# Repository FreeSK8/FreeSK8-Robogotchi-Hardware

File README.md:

# FreeSK8-Robogotchi-Hardware

The [FreeSK8 Robogotchi](https://derelictrobot.com/collections/production/products/freesk8-robogotchi) is an advanced BLE Receiver, Datalogger, and core component of the FreeSK8 System.

Think of it like a blackbox flight recorder for your esk8 or LEV. 

The Robogotchi brings Always-On Logging as a core feature with an asynchronous logging integration with our FreeSK8 Mobile App. 

Ride now, Sync later.

[Robogotchi Documentation @ FreeSK8 Codex](https://codex.freesk8.org/docs/robogotchi)
 
<!-- LICENSE -->
## License

(C) Copyright 2021 - FreeSK8 Foundation NPO

**Licensed under [CERN-OHL-S V2.0](https://ohwr.org/cern_ohl_s_v2.txt)**

https://cern-ohl.web.cern.ch/

<!-- CONTACT -->
## Authors

* Renee Glinski - [@r3n33](https://github.com/r3n33)
* Andrew Dresner - [@DerelictRobot](https://github.com/DerelictRobot)
* Project Link: [https://github.com/FreeSK8](https://github.com/FreeSK8)

 <!-- CONTRIBUTING -->
## Contributing

Contributions are what make the open source community such an amazing place to be learn, inspire, and create. Any contributions you make are **greatly appreciated**.

1. Fork the Project
2. Create your Feature Branch (`git checkout -b feature/AmazingFeature`)
3. Commit your Changes (`git commit -m 'Add some AmazingFeature'`)
4. Push to the Branch (`git push origin feature/AmazingFeature`)
5. Open a Pull Request

<!-- ACKNOWLEDGEMENTS -->
## Attribution & References

* [VESC-Project](https://vesc-project.com)
* [NRF52 VESC](https://github.com/vedderb/nrf52_vesc)
* [Nordic NRF5 SDK](https://infocenter.nordicsemi.com/index.jsp)

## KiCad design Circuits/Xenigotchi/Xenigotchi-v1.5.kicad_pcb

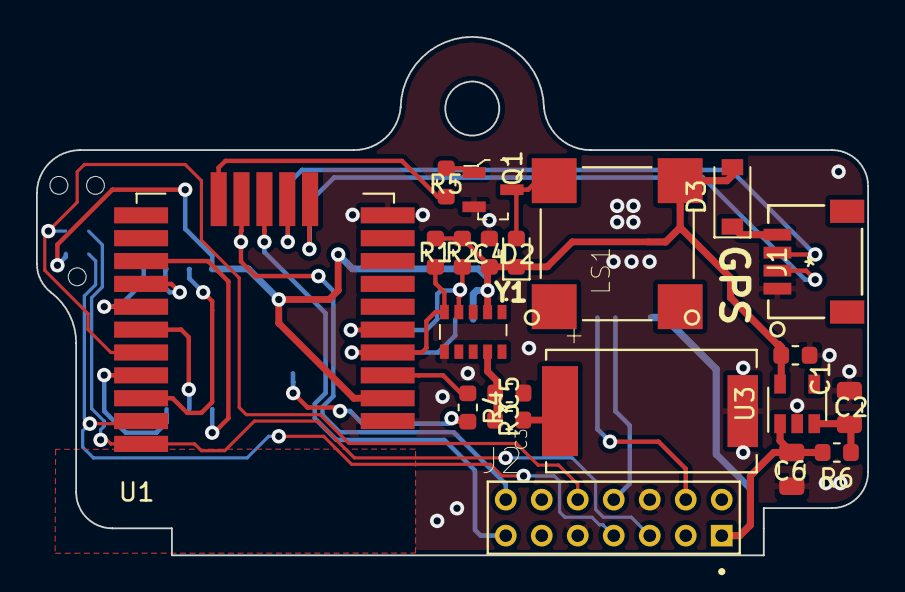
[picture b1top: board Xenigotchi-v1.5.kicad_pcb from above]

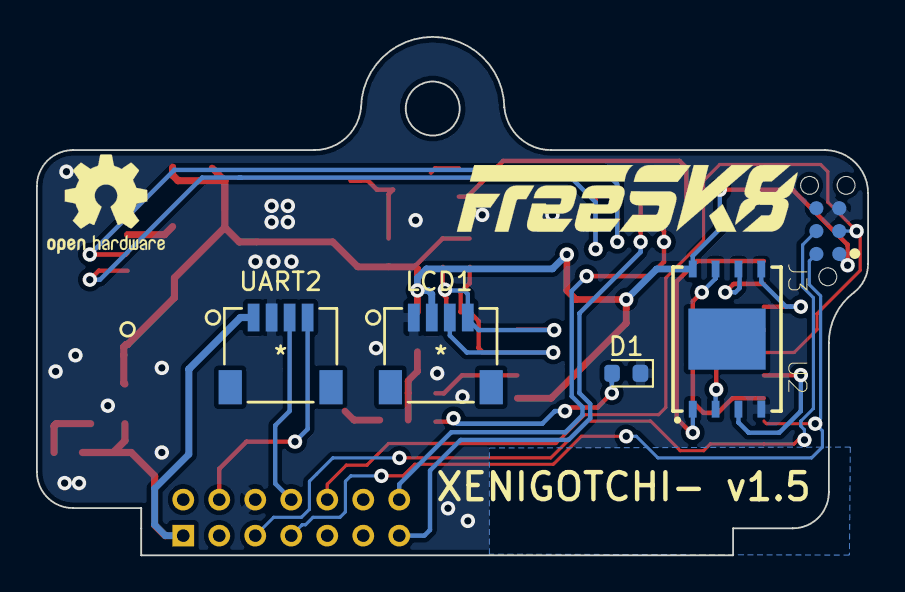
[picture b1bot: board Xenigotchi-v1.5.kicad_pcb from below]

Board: 2 copper layers, 46.2 x 28.8 mm, 26 parts (5 on the bottom side), 29 nets.

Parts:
C1: 1.0uF; C_0603_1608Metric
C2, C6: 10uF; C_0805_2012Metric
C3: DSK-3R3H224U-HL; CAP_DSK-3R3H224U-HL
C4: 0.1uF; C_0603_1608Metric
C5: 10000pF; C_0603_1608Metric
D1: LED; LED_0603_1608Metric
D2: SD0603S040S0R2; D_0603_1608Metric
D3: D_Schottky_Small; D_SOD-123
J1: SM04B-SRSS-TB
J2: 1-1734508-4; TE_1-1734508-4
J3: TC2030-CTX; TAG_TC2030-IDC-NL
LCD1: SM04B-SRSS-TB
LS1: CMT-8503-90-SMT-TR; XDCR_CMT-8503-90-SMT-TR
Q1: 2SD1484KT146R; SOT-23-3
R1, R2: 10k; R_0603_1608Metric
R3: 470r; R_0603_1608Metric
R4: 1k; R_0603_1608Metric
R5: 180r; R_0603_1608Metric
R6: 20k; R_0603_1608Metric
U1: SKB501; SKB501_RF_Module
U2: W25N01GVZEIG_TR; SON127P800X600X80-9N
U3: TLV75533PDBV; SOT-23-5
UART2: SM04B-SRSS-TB
Y1: RV-3129-C3; ABRTCMC32768kHzEOZ9S3DBT

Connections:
+3V3: C1.1, C4.1, D2.1, D3.2, J3.1, LCD1.2, LS1.P, R1.1, R2.1, U1.2, U2.8, U3.5, Y1.2
+5V: C6.1, J2.1, R6.2, U3.1, UART2.1
/ESC-RX: J2.7, U1.13
/ESC-TX: J2.14, U1.14
/GPS-RX: J1.3, U1.12
/GPS-TX: J1.2, U1.11
/P0.05: R4.1, U1.3
/P0.08: R5.2, U1.15
/P0.17: U1.18, U2.1
/P0.19: U1.19, U2.6
/P0.20: U1.20, U2.5
/P0.21: U1.21, U2.2
/P0.22: U1.23, U2.3
/P0.23: U1.24, U2.7
/RST: J2.12, J3.3, U1.22
/SCL: LCD1.4, R2.2, U1.5, Y1.4
/SDA: LCD1.3, R1.2, U1.4, Y1.5
/SWCLK: J2.3, J3.4, U1.26
/SWDIO: J2.4, J3.2, U1.25
/UART2-RX: J2.11, UART2.3
/UART2-TX: J2.9, UART2.4
/VBACKUP: C5.1, R3.1, Y1.9
GND: C1.2, C2.2, C3.2, C4.2, C5.2, C6.2, D1.1, J1.1, J2.5, J2.10, J3.5, LCD1.1, Q1.1, U1.1, U1.10, U2.4, U3.2, UART2.2, Y1.6
unnamed: C2.1, R6.1, U3.3
unnamed: C3.1, R3.2
unnamed: D1.2, R4.2
unnamed: D2.2, LS1.N, Q1.3
unnamed: D3.1, J1.4
unnamed: Q1.2, R5.1

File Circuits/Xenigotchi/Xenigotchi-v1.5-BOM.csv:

Comment,Designator,Footprint,LCSC Part #
"1.0uF Unpolarized capacitor, small symbol",C1,C_0603_1608Metric,
"10uF Unpolarized capacitor, small symbol","C2,C6",C_0805_2012Metric,
DSK-3R3H224U-HL ,C3,CAP_DSK-3R3H224U-HL,
"0.1uF Unpolarized capacitor, small symbol",C4,C_0603_1608Metric,
"10000pF Unpolarized capacitor, small symbol",C5,C_0603_1608Metric,
LED Light emitting diode,D1,LED_0603_1608Metric,
SD0603S040S0R2 Schottky diode,D2,D_0603_1608Metric,
"D_Schottky_Small Schottky diode, small symbol",D3,D_SOD-123,
SM04B-SRSS-TB ,"J1,LCD1,UART2",SM04B-SRSS-TB,
1-1734508-4 ,J2,TE_1-1734508-4,
TC2030-CTX ,J3,TAG_TC2030-IDC-NL,
CMT-8503-90-SMT-TR ,LS1,XDCR_CMT-8503-90-SMT-TR,
2SD1484KT146R ,Q1,SOT-23-3,
"10k Resistor, small US symbol","R1,R2",R_0603_1608Metric,
"470r Resistor, small US symbol",R3,R_0603_1608Metric,
"1k Resistor, small US symbol",R4,R_0603_1608Metric,
"180r Resistor, small US symbol",R5,R_0603_1608Metric,
"20k Resistor, small US symbol",R6,R_0603_1608Metric,
SKB501 ,U1,SKB501_RF_Module,
W25N01GVZEIG_TR ,U2,SON127P800X600X80-9N,
"TLV75533PDBV 500mA Low Dropout Voltage Regulator, Fixed Output 3.3V, SOT-23-5",U3,SOT-23-5,
RV-3129-C3 ,Y1,ABRTCMC32768kHzEOZ9S3DBT,

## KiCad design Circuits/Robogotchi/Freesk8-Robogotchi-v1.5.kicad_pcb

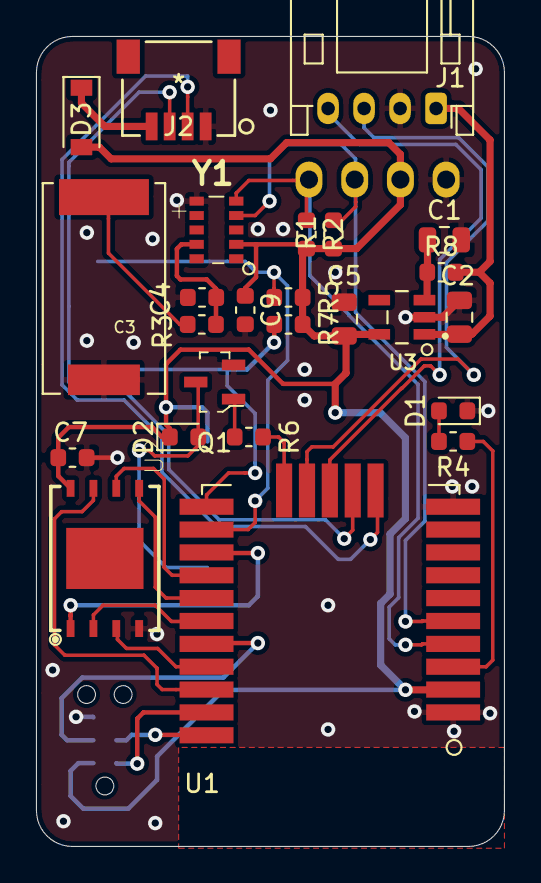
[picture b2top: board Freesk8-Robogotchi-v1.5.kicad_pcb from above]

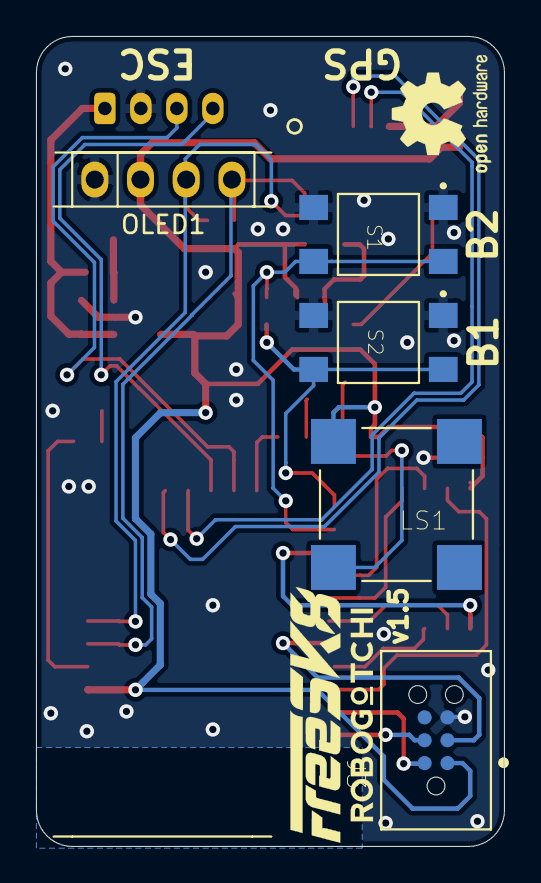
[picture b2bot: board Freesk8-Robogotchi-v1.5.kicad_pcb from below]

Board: 2 copper layers, 26.0 x 45.0 mm, 30 parts (5 on the bottom side), 29 nets.

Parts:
C1: 10uF; C_0805_2012Metric
C2, C5: 1uF; C_0805_2012Metric
C3: DSK-3R3H224U-HL; CAP_DSK-3R3H224U-HL
C4: 10000pF; C_0603_1608Metric
C7, C9: 0.1uF; C_0603_1608Metric
D1: LED; LED_0603_1608Metric
D2: SD0603S040S0R2; D_0603_1608Metric
D3: B130-E3; D_SOD-123
J1: S4B-PH-K-SLFSN; JST_PH_S4B-PH-K_1x04_P2.00mm_Horizontal
J2: SM04B-SRSS-TB
J3: TC2030-CTX; TAG_TC2030-IDC-NL
LS1: CMT-8503-90-SMT-TR; XDCR_CMT-8503-90-SMT-TR
OLED1: OLED-0.91; OLED-0.9
Q1: 2SD1484KT146R; SOT-23-3-R
R1, R2, R5, R7: 10k; R_0603_1608Metric
R3: 470r; R_0603_1608Metric
R4: 1k; R_0603_1608Metric
R6: 180r; R_0603_1608Metric
R8: 20k; R_0603_1608Metric
S1, S2: TL3315NF160Q; SW_TL3305AF260QG
U1: SKB501; SKB501_RF_Module
U2: MX25L25645GZ2I-08G; SON127P800X600X80-9N
U3: TLV75533PDBVR; SOT95P280X145-5N
Y1: RV-3129-C3; ABRTCMC32768kHzEOZ9S3DBT

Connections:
+3V3: C5.1, C7.1, C9.1, D2.1, D3.2, J3.1, LS1.P, OLED1.2, R1.1, R2.1, R5.1, R7.1, U1.2, U2.8, U3.5, Y1.2
+5V: C2.1, J1.1, R8.2, U3.1
/ESC-RX: J1.3, U1.14
/ESC-TX: J1.4, U1.13
/GPS-RX: J2.3, U1.12
/GPS-TX: J2.2, U1.11
/P0.05: R4.1, U1.3
/P0.08: R6.2, U1.15
/P0.09: R7.2, S2.3, S2.4, U1.16
/P0.10: R5.2, S1.3, S1.4, U1.17
/P0.17: U1.18, U2.1
/P0.19: U1.19, U2.6
/P0.20: U1.20, U2.5
/P0.21: U1.21, U2.2
/P0.22: U1.23, U2.3
/P0.23: U1.24, U2.7
/RST: J3.3, U1.22
/SCL: OLED1.3, R2.2, U1.5, Y1.4
/SDA: OLED1.4, R1.2, U1.4, Y1.5
/SWCLK: J3.4, U1.26
/SWDIO: J3.2, U1.25
/VBACKUP: C4.1, R3.1, Y1.9
GND: C1.2, C2.2, C3.2, C4.2, C5.2, C7.2, C9.2, D1.1, J1.2, J2.1, J3.5, OLED1.1, Q1.1, S1.1, S1.2, S2.1, S2.2, U1.1, U1.10, U2.4, U3.2, Y1.6
unnamed: C1.1, R8.1, U3.3
unnamed: C3.1, R3.2
unnamed: D1.2, R4.2
unnamed: D2.2, LS1.N, Q1.3
unnamed: D3.1, J2.4
unnamed: Q1.2, R6.1

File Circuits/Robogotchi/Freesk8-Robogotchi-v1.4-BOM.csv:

"Id";"Designator";"Package";"Quantity";"Designation";"Supplier and ref";
1;"Q1";"SOT-23-3-R";1;"2SD1484KT146R";;;
2;"G***";"FreeSK8-Logo-14x3.5mm";1;"LOGO";;;
3;"OLED1";"OLED-0.9";1;"OLED-0.91";;;
4;"C7,C9";"C_0603_1608Metric";2;"0.1uF";;;
5;"J3";"TAG_TC2030-IDC-NL";1;"TC2030-CTX";;;
6;"S2,S1";"SW_TL3305AF260QG";2;"TL3315NF160Q";;;
7;"C3";"CAP_DSK-3R3H224U-HL";1;"DSK-3R3H224U-HL";;;
8;"Y1";"ABRTCMC32768kHzEOZ9S3DBT";1;"RV-3129-C3";;;
9;"J2,J1";"JST_PH_S4B-PH-K_1x04_P2.00mm_Horizontal";2;"S4B-PH-K-SLFSN";;;
10;"C5,C2";"C_0805_2012Metric";2;"10uF";;;
11;"C4";"C_0603_1608Metric";1;"10000pF";;;
12;"LS1";"XDCR_CMT-8503-90-SMT-TR";1;"CMT-8503-90-SMT-TR";;;
13;"R6";"R_0603_1608Metric";1;"180r";;;
14;"D2,D3";"D_0603_1608Metric";2;"SD0603S040S0R2";;;
15;"D1";"LED_0603_1608Metric";1;"LED";;;
16;"R4";"R_0603_1608Metric";1;"1k";;;
17;"U2";"SON127P800X600X80-9N";1;"MX25L25645GZ2I-08G";;;
18;"R7,R1,R2,R5";"R_0603_1608Metric";4;"10k";;;
19;"C1,C6";"C_0603_1608Metric";2;"1.0uF";;;
20;"R3";"R_0603_1608Metric";1;"470r";;;
21;"IC1";"SON65P200X200X80-7N";1;"LP5912-3.3DRVR";;;
22;"U1";"SKB501_RF_Module";1;"SKB501";;;

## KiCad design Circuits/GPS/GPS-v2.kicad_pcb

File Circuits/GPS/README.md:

## GPS v1.3 utilizes an off the shelf GPS solution, such as the BN-220 GPS Module.

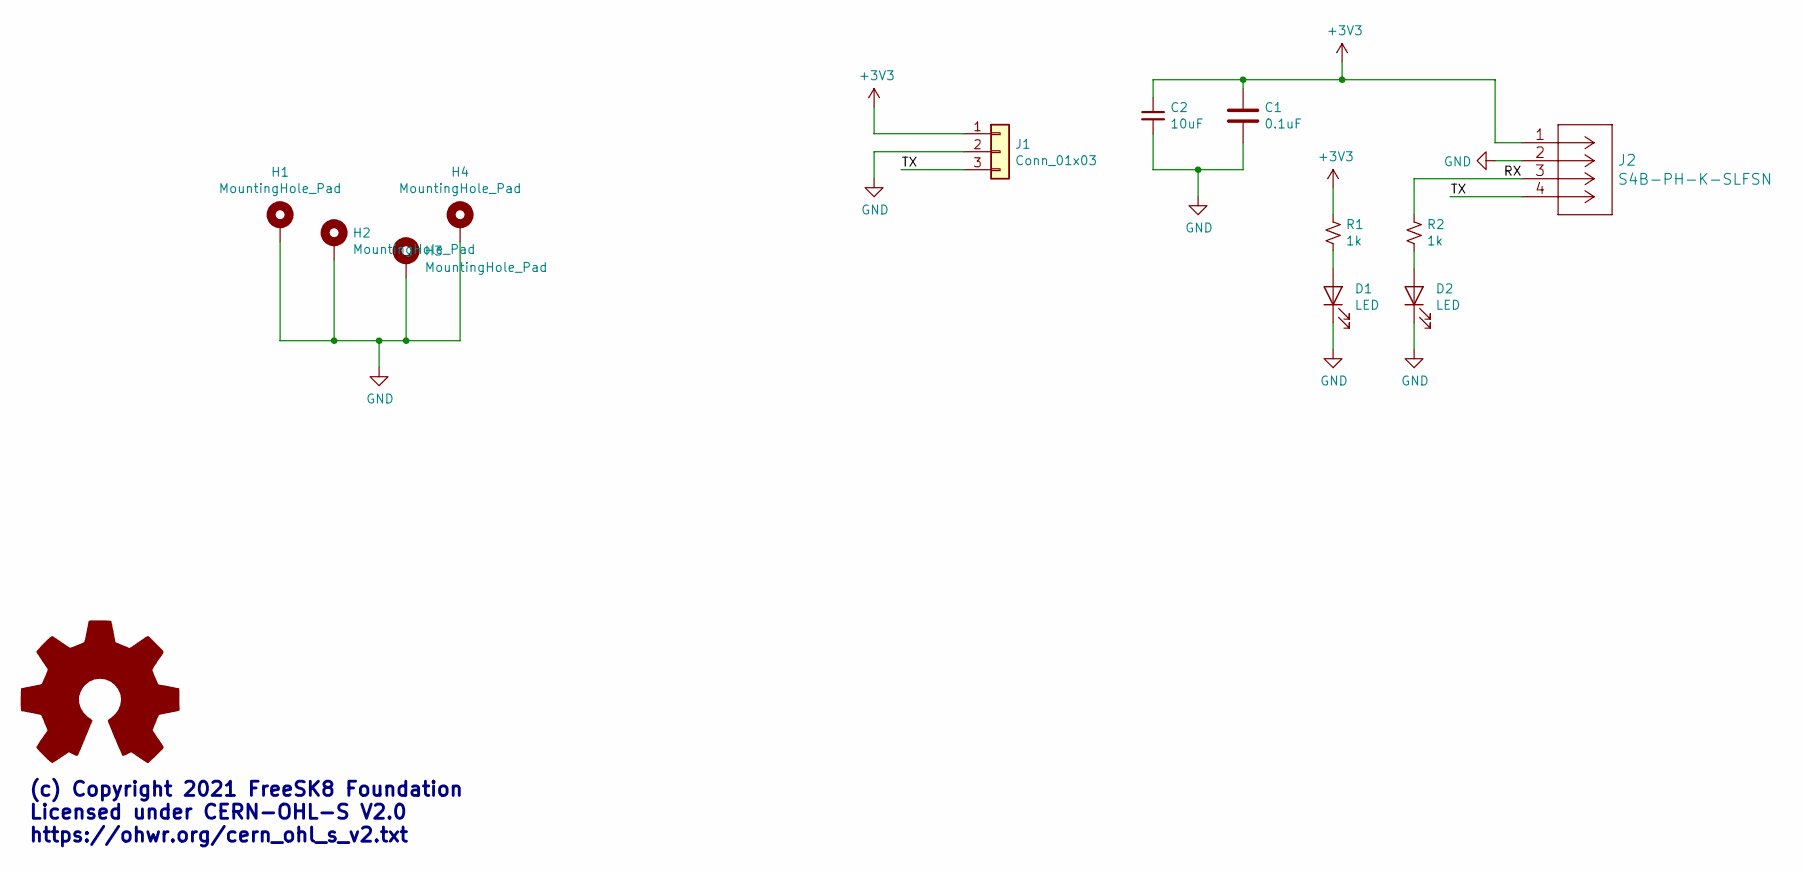
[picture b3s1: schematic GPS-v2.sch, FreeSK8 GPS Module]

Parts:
C1: 0.1uF; C_0603_1608Metric
C2: 10uF; C_0805_2012Metric
D1, D2: LED; LED_0603_1608Metric
H1, H2, H3, H4: MountingHole_Pad; MountingHole_2.5mm_Pad
J1: Conn_01x03; JST_SH_SM03B-SRSS-TB_1x03-1MP_P1.00mm_Horizontal
J2: S4B-PH-K-SLFSN; JST_PH_S4B-PH-K_1x04_P2.00mm_Horizontal
R1, R2: 1k; R_0603_1608Metric

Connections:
+3V3: C1.1, C2.1, J1.1, J2.1, R1.1
/RX: J2.3, R2.1
/TX: J1.3, J2.4
GND: C1.2, C2.2, D1.1 (K), D2.1 (K), H1.1, H2.1, H3.1, H4.1, J1.2, J2.2
unnamed: D1.2 (A), R1.2
unnamed: D2.2 (A), R2.2

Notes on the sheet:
(c) Copyright 2021 FreeSK8 Foundation Licensed under CERN-OHL-S V2.0 https://ohwr.org/cern_ohl_s_v2.txt

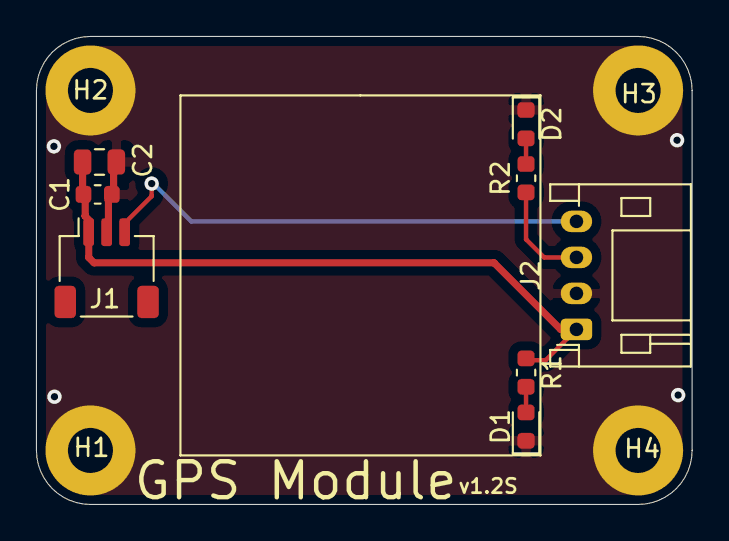
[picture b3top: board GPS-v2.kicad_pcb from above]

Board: 2 copper layers, 36.4 x 26.0 mm, 12 parts (0 on the bottom side), 6 nets.

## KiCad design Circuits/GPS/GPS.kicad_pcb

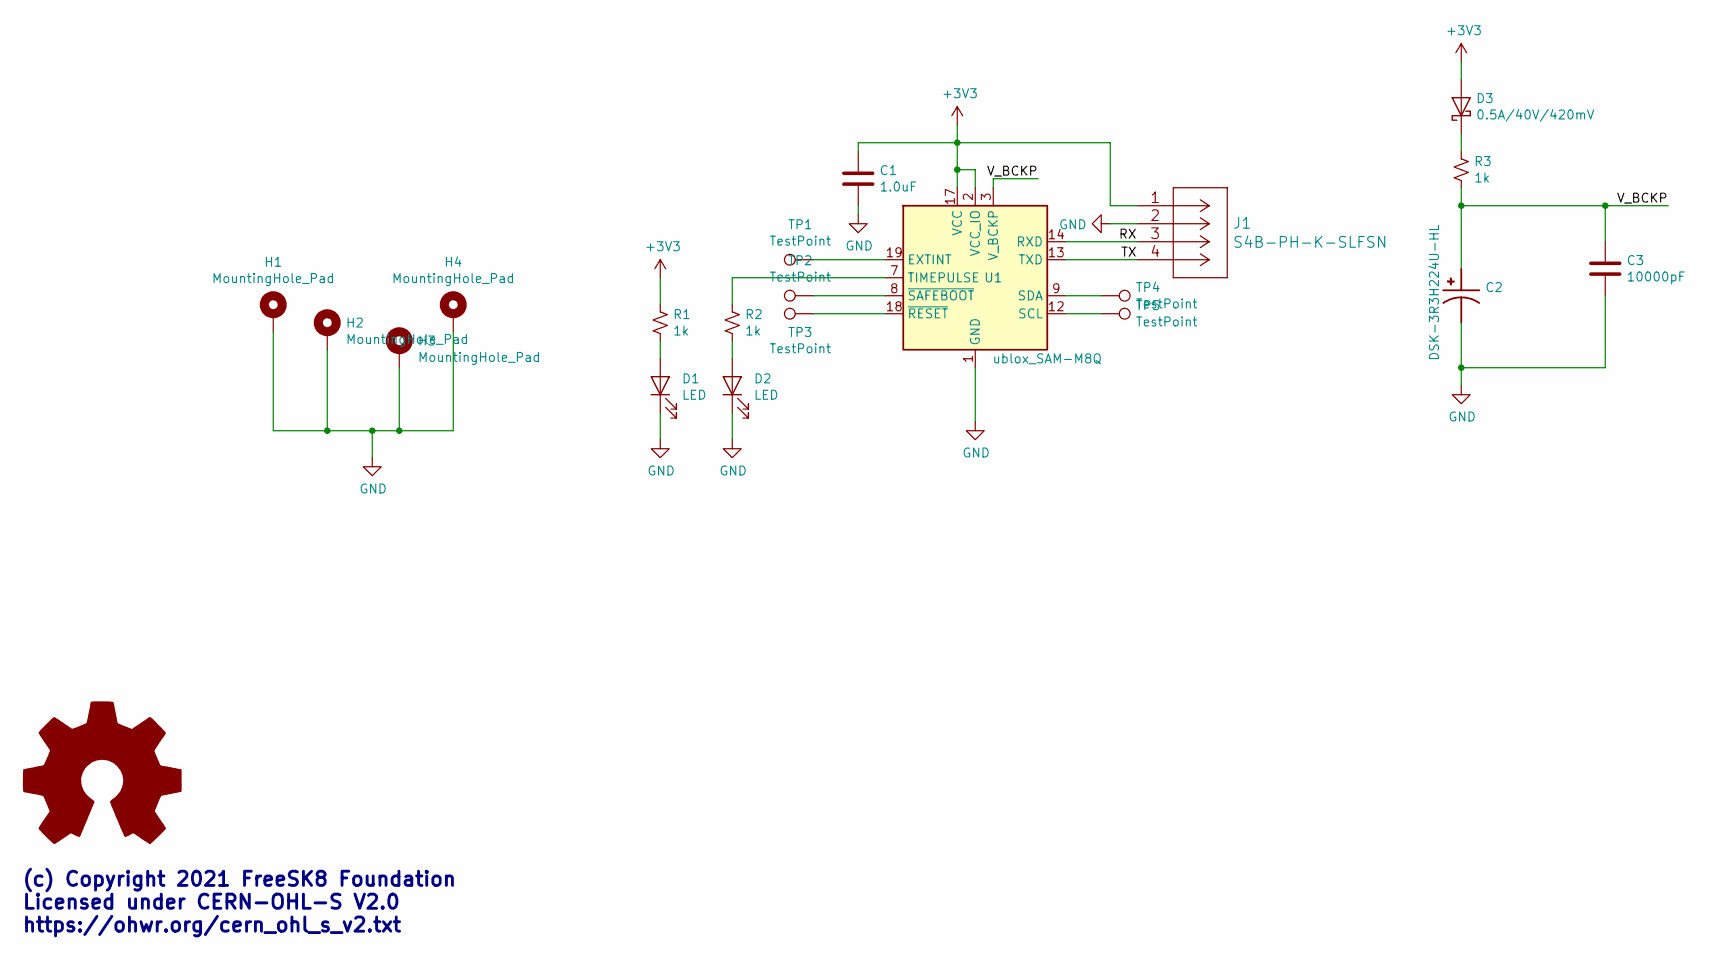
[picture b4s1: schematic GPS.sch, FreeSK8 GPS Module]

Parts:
C1: 1.0uF; C_0603_1608Metric
C2: DSK-3R3H224U-HL; CAP_DSK-3R3H224U-HL
C3: 10000pF; C_0603_1608Metric
D1, D2: LED; LED_0603_1608Metric
D3: 0.5A/40V/420mV; D_0603_1608Metric
H1, H2, H3, H4: MountingHole_Pad; MountingHole_2.5mm_Pad
J1: S4B-PH-K-SLFSN; JST_PH_S4B-PH-K_1x04_P2.00mm_Horizontal
R1, R2, R3: 1k; R_0603_1608Metric
TP1, TP2, TP3, TP4, TP5: TestPoint; TestPoint_Pad_1.0x1.0mm
U1: ublox_SAM-M8Q; ublox_SAM-M8Q_HandSolder

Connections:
+3V3: C1.1, D3.2 (A), J1.1, R1.1, U1.2 (VCC_IO), U1.17 (VCC)
/RX: J1.3, U1.14 (RXD)
/TX: J1.4, U1.13 (TXD)
/V_BCKP: C2.1, C3.1, R3.2, U1.3 (V_BCKP)
GND: C1.2, C2.2, C3.2, D1.1 (K), D2.1 (K), H1.1, H2.1, H3.1, H4.1, J1.2, U1.1 (GND), U1.4 (GND), U1.5 (GND), U1.6 (GND), U1.10 (GND), U1.11 (GND), U1.15 (GND), U1.16 (GND), U1.20 (GND)
unnamed: D1.2 (A), R1.2
unnamed: D2.2 (A), R2.2
unnamed: D3.1 (K), R3.1
unnamed: R2.1, U1.7 (TIMEPULSE)
unnamed: TP1.1, U1.19 (EXTINT)
unnamed: TP2.1, U1.8 (~SAFEBOOT)
unnamed: TP3.1, U1.18 (~RESET)
unnamed: TP4.1, U1.9 (SDA)
unnamed: TP5.1, U1.12 (SCL)

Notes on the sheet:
(c) Copyright 2021 FreeSK8 Foundation Licensed under CERN-OHL-S V2.0 https://ohwr.org/cern_ohl_s_v2.txt

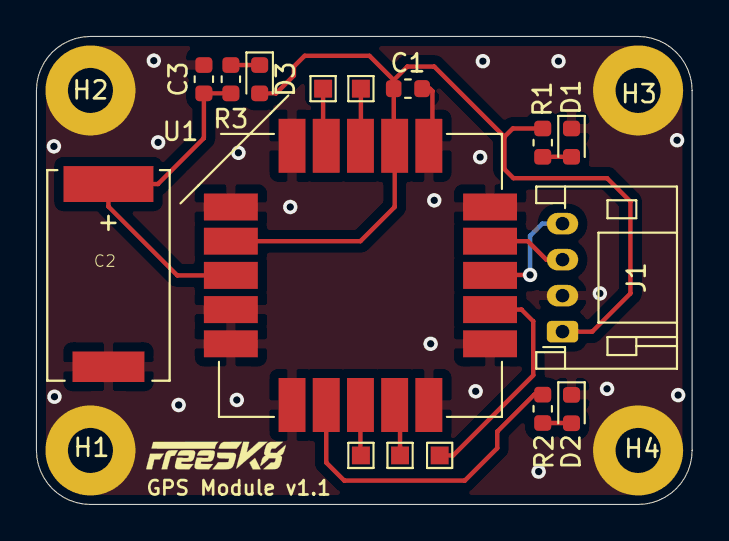
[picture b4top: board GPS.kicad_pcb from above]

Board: 2 copper layers, 36.4 x 26.0 mm, 20 parts (0 on the bottom side), 14 nets.

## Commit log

2020-10-11 Initial commit of drawings
2020-10-22 GPS Module & Enclosure models
2020-11-01 Adding Diagrams
2020-11-02 flipped tx/rx pinout on gotchi
2020-11-02 Added Schematics + dimensional drawings.
2020-11-02 added xray image
2020-11-03 GPS Module schematic & docs
2020-11-07 Reorg docs & models
2020-11-11 Robogotchi Enclosure upload/first commit
    3 pieces, top & bottom shell + buttons
2020-11-11 Added Robogotchi Enclosure images
2020-11-12 rev0.2 updates to enclosure, file cleanup
2020-11-12 doc image updates
2020-11-12 Adjusted top-enclosure OLED window
2020-11-17 Minor button/hole clearance updates
2020-11-18 Minor changes to internal features for print quality
2020-11-19 firmware update documentation/images
2021-05-07 License update to CERN OHL v2.0 prior to prepare for full source release
2021-05-15 Rename Schematics folder to Circuits
2021-05-27 Updated GPS Enclosure STL + ASM of entire assembly
2021-06-02 v1.4 Robogotchi Schematic update
2021-07-27 Robogotchi KiCAD Design source, initial upload.
    Here we gooooo!
2021-07-27 added GPS schematic
2021-07-27 Xenigotchi v1.3 schematic PDF
2021-08-13 Robogotchi & Xenigotchi v1.5 updates
    Added gerbers + changed GPS headers to JST SM 1.0mm pitch connectors.
2021-08-14 Docs/renders upload
2021-08-14 Add GPS v1.3 enclosure
    Using BN-220 GPS module for v1.3 for simplicity & cost savings.
2021-08-14 cleanup

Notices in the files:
parts and their libraries:
Copyright 2016 Accelerated Designs. All rights reserved.
